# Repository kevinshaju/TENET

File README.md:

# __TENET__
WIRELESS DEVELOPMENT BOARD DESIGN

TENET is development board specifically designed for beginners and enthusiasts in the field of IoT and Robotics. At the heart of the board is the NINA-B302 microcontroller unit. The board also features the ESP-12F wireless chip for wireless connectivity. Incase if you're wondering how is it any different from other boards out there, then have a closer look at the design. TENET has an inbuilt DRV8833 motordriver which can be used to connect upto 2 motors without the need for any external shields. The board also has a Li-Po charging unit that can be used to power the board using a single cell Li-Po battery, which will come in handy while prototyping your next wireless robot.

The board also has quite a few sensors that you might need for your integrated Iot project. The details of all the features of the board are provided below:

1) 16 GPIO Headers
2) LSM9DS1-iNEMO Inertial Module
3) DRV8833 dual-H Bridge Motor Driver
4) LPS25HB Pressure Sensor
5) APDS-9960 Digital Proximity, Ambient Light, RGB and Gesture Sensor
6) HTS221 Capacitive digital sensor for relative humidity and temperature
7) ESP-12F WiFi Module

##  *"With TENET the only limit is your own imagination."*

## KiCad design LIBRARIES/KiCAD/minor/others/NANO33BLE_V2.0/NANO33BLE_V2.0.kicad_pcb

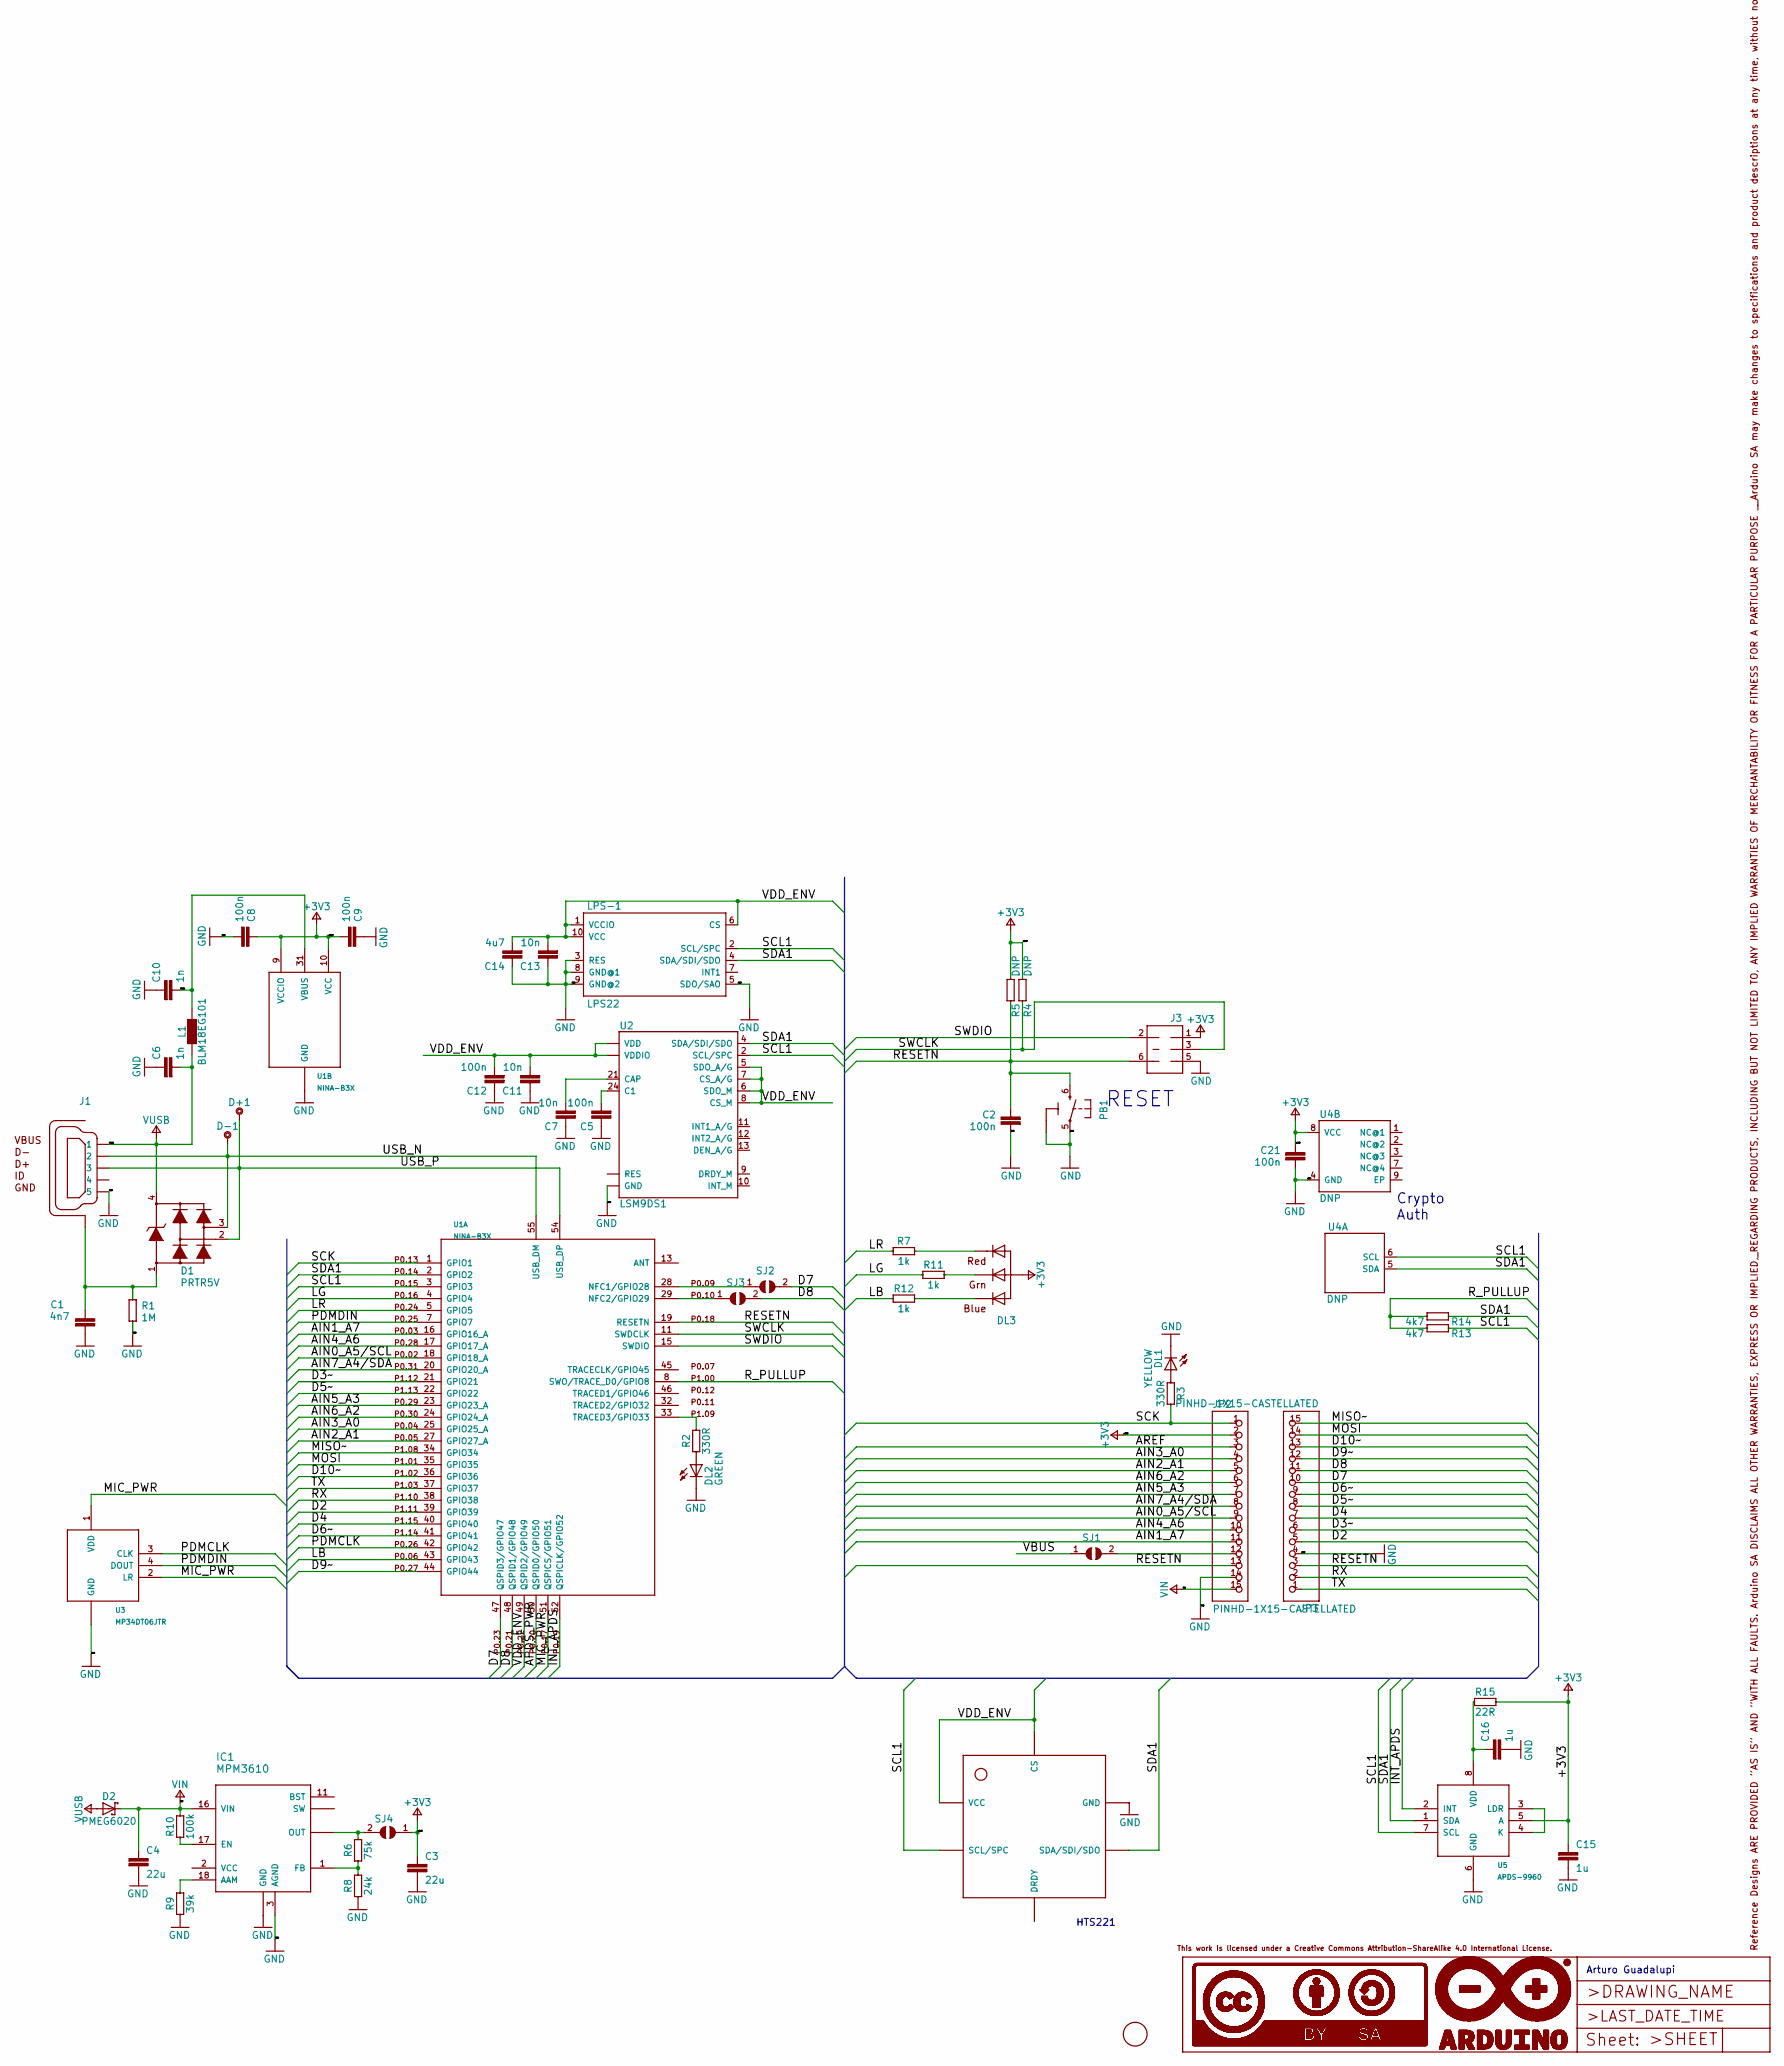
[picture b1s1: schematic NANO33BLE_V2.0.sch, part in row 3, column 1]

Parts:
C1: 4n7; 0805-R2013X50N; VOLTAGE 1KV
C2, C5, C8, C9, C12, C21: 100n; 0402-1005X55N
C3, C4: 22u; 0805-R2013X50N
C6, C10: 1n; 0402-1005X55N
C7, C11, C13: 10n; 0402-1005X55N
C14: 4u7; 0402-1005X55N
C15, C16: 1u; 0402-1005X55N
D1: PRTR5V; SOT190P230X110-4N
D2: PMEG6020; SODFL3517X110N
D+1: DNP; TP-1.00MM
D-1: DNP; TP-1.00MM
DL1: YELLOW; LEDC1608X80N-AK
DL2: GREEN; LEDC1608X80N-AK
DL3: -; SMLP34RGB2W
FD1: DNP; FD-1-1.5
FRAME1: DNP; FRAME
HS-1: HTS221
IC1: MPM3610
J1: -; ZX62-AB-5PA
J3: DNP; 2X03-TP1
JP2, JP3: PINHD-1X15-CASTELLATED; 1X15-CASTELL
L1: BLM18EG101; 0603-1608X90N
LPS-1: LPS22; LPS22H
PB1: PTS820; C&K_PTS820_NO_HOLES
R1: 1M; 0402-1005X55N
R2, R3: 330R; 0402-1005X55N
R4, R5: DNP; 0402-1005X55N
R6: 75k; 0402-1005X55N
R7, R11, R12: 1k; 0402-1005X55N
R8: 24k; 0402-1005X55N
R9: 39k; 0402-1005X55N
R10: 100k; 0402-1005X55N
R13, R14: 4k7; 0402-1005X55N
R15: 22R; 0402-1005X55N
SJ1, SJ2, SJ3, SJ4: DNP; SJ
U1: NINA-B3X
U2: LSM9DS1; LSM9DS1_TEMP_LGA24-8X4
U3: MP34DT06JTR; HCLGA
U4: DNP; SON50P300X200X60-9N-EP160X140
U5: APDS-9960; APDS9960

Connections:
+3V3: C3.1, C8.1, C9.2, C15.1, C21.1, DL3.1 (A), J3.1, JP2.2, R4.2, R5.2, R15.2, SJ4.1, U1.9 (VCCIO), U1.10 (VCC), U4.8 (VCC), U5.5 (A)
/AIN0_A5/SCL: JP2.9, U1.18 (GPIO18_A)
/AIN1_A7: JP2.11, U1.16 (GPIO16_A)
/AIN2_A1: JP2.5, U1.27 (GPIO27_A)
/AIN3_A0: JP2.4, U1.25 (GPIO25_A)
/AIN4_A6: JP2.10, U1.17 (GPIO17_A)
/AIN5_A3: JP2.7, U1.23 (GPIO23_A)
/AIN6_A2: JP2.6, U1.24 (GPIO24_A)
/AIN7_A4/SDA: JP2.8, U1.20 (GPIO20_A)
/APDS_PWR: U1.50 (QSPID0/GPIO50)
/AREF: JP2.3
/D2: JP3.5, U1.39 (GPIO39)
/D3~~: JP3.6, U1.21 (GPIO21)
/D4: JP3.7, U1.40 (GPIO40)
/D5~~: JP3.8, U1.22 (GPIO22)
/D6~~: JP3.9, U1.41 (GPIO41)
/D7: JP3.10, SJ2.2, U1.47 (QSPID3/GPIO47)
/D8: JP3.11, SJ3.2, U1.48 (QSPID1/GPIO48)
/D9~~: JP3.12, U1.44 (GPIO44)
/D10~~: JP3.13, U1.36 (GPIO36)
/INT_APDS: U1.52 (QSPICLK/GPIO52), U5.2 (INT)
/LB: R12.1, U1.43 (GPIO43)
/LG: R11.1, U1.4 (GPIO4)
/LR: R7.1, U1.5 (GPIO5)
/MIC_PWR: U1.51 (QSPICS/GPIO51), U3.1 (VDD), U3.2 (LR)
/MISO~~: JP3.15, U1.34 (GPIO34)
/MOSI: JP3.14, U1.35 (GPIO35)
/PDMCLK: U1.42 (GPIO42), U3.3 (CLK)
/PDMDIN: U1.7 (GPIO7), U3.4 (DOUT)
/RESETN: C2.1, J3.6, JP2.13, JP3.3, PB1.6 (2), R5.1, U1.19 (RESETN)
/RX: JP3.2, U1.38 (GPIO38)
/R_PULLUP: R13.2, R14.2, U1.8 (SWO/TRACE_D0/GPIO8)
/SCK: JP2.1, R3.2, U1.1 (GPIO1)
/SCL1: HS-1.P$2.SCL/SPC (SCL/SPC), LPS-1.2 (SCL/SPC), R13.1, U1.3 (GPIO3), U2.2 (SCL/SPC), U4.6 (SCL), U5.7 (SCL)
/SDA1: HS-1.P$4.SDA/SDI/SDO (SDA/SDI/SDO), LPS-1.4 (SDA/SDI/SDO), R14.1, U1.2 (GPIO2), U2.4 (SDA/SDI/SDO), U4.5 (SDA), U5.1 (SDA)
/SWCLK: J3.3, R4.1, U1.11 (SWDCLK)
/SWDIO: J3.2, U1.15 (SWDIO)
/TX: JP3.1, U1.37 (GPIO37)
/USB_N: D1.3, D-1.X, J1.2, U1.55 (USB_DM)
/USB_P: D1.2, D+1.X, J1.3, U1.54 (USB_DP)
/VBUS: C10.2, L1.2, SJ1.1, U1.31 (VBUS)
/VDD_ENV: C11.2, C12.2, C13.2, C14.2, HS-1.P$1.VDD (VCC), HS-1.P$6.CS (CS), LPS-1.1 (VCCIO), LPS-1.6 (CS), LPS-1.10 (VCC), U1.49 (QSPID2/GPIO49), U2.1 (VDDIO), U2.3 (VDDIO), U2.5 (SDO_A/G), U2.6 (SDO_M), U2.7 (CS_A/G), U2.8 (CS_M), U2.22 (VDD), U2.23 (VDD)
GND: C1.2, C2.2, C3.2, C4.2, C5.1, C6.1, C7.1, C8.2, C9.1, C10.1, C11.1, C12.1, C13.1, C14.1, C15.2, C16.2, C21.2, DL1.C, DL2.C, HS-1.P$5.GND (GND), IC1.3 (AGND), IC1.12 (GND), IC1.13 (GND), IC1.14 (GND), J1.5, J3.5, JP2.14, JP3.4, LPS-1.3 (RES), LPS-1.5 (SDO/SAO), LPS-1.8 (GND@1), LPS-1.9 (GND@2), PB1.1 (3), PB1.2 (3), PB1.3, PB1.4 (3), PB1.5 (1), R1.1, R8.1, R9.1, U1.6 (GND), U1.12 (GND), U1.14 (GND), U1.26 (GND), U1.30 (GND), U1.53 (GND), U1.GND@1 (GND), U1.GND@2 (GND), U1.GND@3 (GND), U1.GND@4 (GND), U1.GND@5 (GND), U1.GND@6 (GND), U1.GND@7 (GND), U1.GND@8 (GND), U1.GND@9 (GND), U1.GND@10 (GND), U1.GND@11 (GND), U1.GND@12 (GND), U2.19 (GND), U2.20 (GND), U3.GND, U3.GND@2 (GND), U3.GND@3 (GND), U3.GND@4 (GND), U4.4 (GND), U5.6 (GND)
unnamed: C1.1, D1.1, J1.6 (SH), J1.7 (SH), J1.8 (SH), J1.9 (SH), J1.10 (SH), J1.11 (SH), R1.2
unnamed: C5.2, U2.24 (C1)
unnamed: C7.2, U2.21 (CAP)
unnamed: C16.1, R15.1, U5.8 (VDD)
unnamed: DL1.A, R3.1
unnamed: DL2.A, R2.1
unnamed: DL3.2 (RED_C), R7.2
unnamed: DL3.3 (BLUE_C), R12.2
unnamed: DL3.4 (GREEN_C), R11.2
unnamed: IC1.1 (FB), R6.1, R8.2
unnamed: IC1.17 (EN), R10.1
unnamed: IC1.18 (AAM), R9.2
unnamed: IC1.4 (SW), IC1.5 (SW), IC1.6 (SW), IC1.19 (SW)
unnamed: IC1.7 (OUT), IC1.8 (OUT), IC1.9 (OUT), IC1.20 (OUT), R6.2, SJ4.2
unnamed: JP2.12, SJ1.2
unnamed: R2.2, U1.33 (TRACED3/GPIO33)
unnamed: SJ2.1, U1.28 (NFC1/GPIO28)
unnamed: SJ3.1, U1.29 (NFC2/GPIO29)
unnamed: U2.14 (RES), U2.15 (RES), U2.16 (RES), U2.17 (RES), U2.18 (RES)
unnamed: U5.3 (LDR), U5.4 (K)
VIN: C4.1, D2.C, IC1.16 (VIN), JP2.15, R10.2
VUSB: C6.2, D1.4, D2.A, J1.1, L1.1

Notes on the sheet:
RESET
Crypto Auth
Arturo Guadalupi
HTS221

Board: 2 copper layers, 58 parts (0 on the bottom side), 63 nets, no tracks yet.

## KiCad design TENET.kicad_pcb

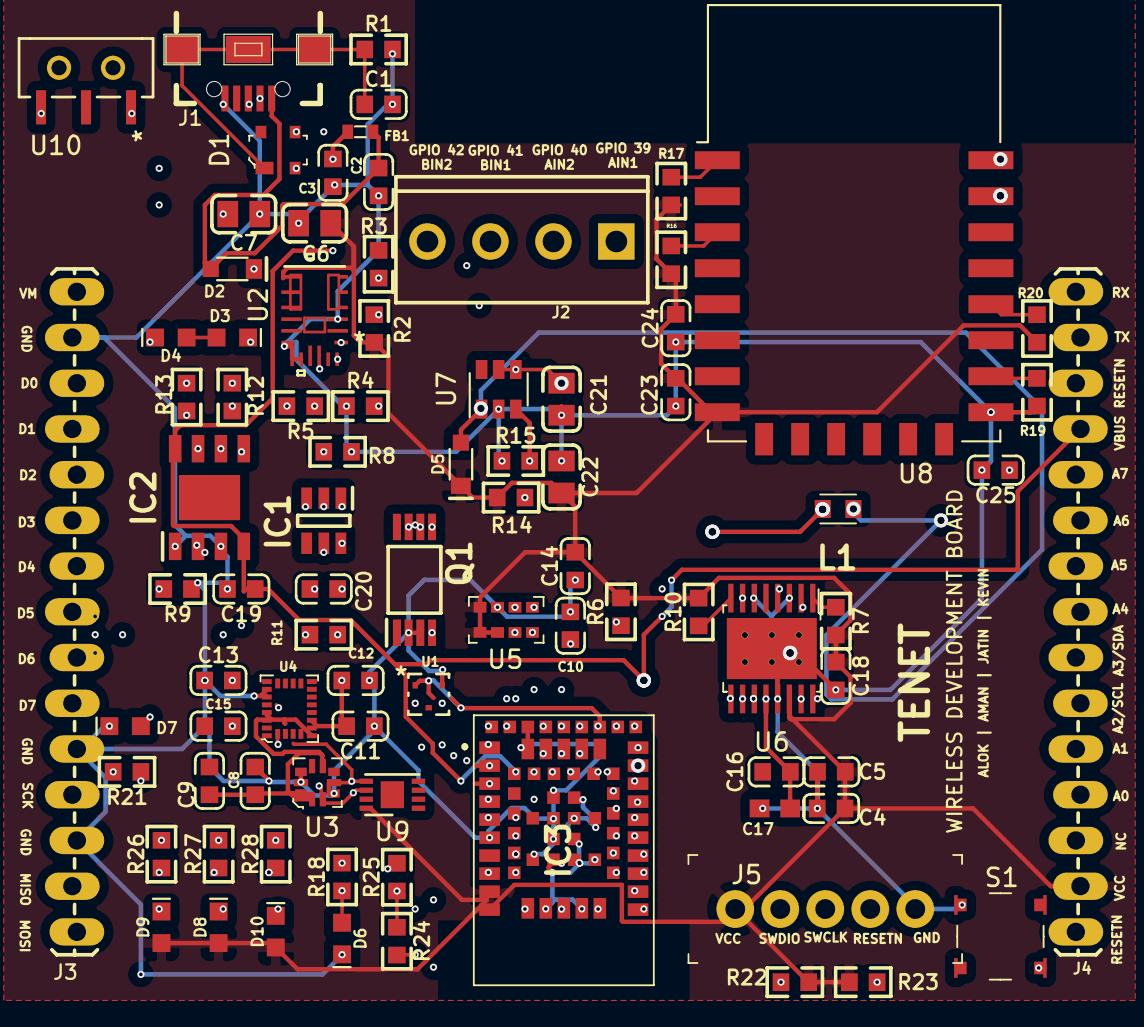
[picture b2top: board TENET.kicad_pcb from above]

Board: 4 copper layers, 86 parts (1 on the bottom side), 83 nets.

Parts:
C1, C2, C3, C4, C5, C8, C9, C10, C11, C12, C13, C14, C15, C16, C18, C19, C20, C23, C24, C25: C_0603
C6, C7, C21, C22: C_0805
C17: 0603-POLAR
D1: TO-253-4
D2, D5: PANASONIC_SMINI2-F5-B
D3, D4, D6, D7, D8, D9, D10: LED-0603
FB1: BLM18PG121SN1D; 0603
IC1: SOT95P280X145-6N
IC2: SOIC127P600X175-9N
IC3: NINAB30200B00
J1: USB-B-MICRO-SMD
J2: SCREWTERMINAL-3.5MM-4
J3, J4: 1X15_LOCK_LONGPADS
J5: PinHeader_1x5_P2.5mm_Drill1.1mm
J6: JST-2-SMD
L1: LQH2MCN100K02L
Q1: SOP65P640X120-8N
R1, R2, R3, R4, R5, R6, R7, R8, R9, R10, R11, R12, R13, R14, R15, R16, R17, R18, R19, R20, R21, R22, R23, R24, R25, R26, R27, R28: R_0603
S1: Switch_Tactile_SMD_4.5x4.5mm_TL3315NF160Q
U1: HTS221TR
U2: MPM3610AGQV-Z
U3: LLGA-10_2.5x2.5mm_LPS25HB
U4: LGA-24_3x3.5mm_LSM9DS1
U5: Ambient_Prox_APDS-9960
U6: TSSOP-16-1EP_W4.40mm
U7: SOT-23-6
U8: ESP-12E
U9: DFN-8-1EP_3x2mm_P0.5mm_EP1.3x1.5mm
U10: AYZ0102AGRLC

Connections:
A0: IC3.16, J4.4
A1: IC3.17, J4.5
A2\SCL: IC3.18, J4.6
A3\SDA: IC3.20, J4.7
A4: IC3.23, J4.8
A5: IC3.24, J4.9
A6: IC3.25, J4.10
A7: IC3.27, J4.11
AIN1: IC3.39, U6.16
AIN2: IC3.40, U6.15
BAT+: IC2.5, J6.2, R11.1, U10.3
BAT-: C20.2, IC1.6, J6.1, Q1.6, Q1.7
BIN1: IC3.41, U6.9
BIN2: IC3.42, U6.10
D0: IC3.21, J3.3
D1: IC3.22, J3.4
D2: IC3.28, J3.5
D3: IC3.29, J3.6
D4: IC3.36, J3.7
D5: IC3.44, J3.8
D6: IC3.47, J3.9
D7: IC3.48, J3.10
D+: D1.2, IC3.54, J1.D+
D-: D1.3, IC3.55, J1.D-
GND: C1.2, C2.1, C3.1, C4.1, C5.2, C6.1, C7.1, C8.1, C9.1, C10.2, C11.1, C12.1, C13.1, C14.1, C15.1, C17.-, C18.2, C19.2, C21.1, C22.1, C23.2, C24.1, C25.2, D6.C, D7.C, IC2.1, IC2.3, IC3.6, IC3.12, IC3.14, IC3.26, IC3.30, IC3.53, IC3.G1, IC3.G2, IC3.G3, IC3.G4, IC3.G5, IC3.G6, IC3.G7, IC3.G8, IC3.G9, IC3.G10, IC3.G11, IC3.G12, J1.GND, J3.2, J3.11, J3.13, J5.5, Q1.2, Q1.3, R1.2, R3.1, R4.1, R8.1, R9.1, R15.1, R19.2, S1.4, U1.5, U2.3, U2.12, U2.13, U2.14, U3.3, U3.5, U3.8, U3.9, U4.19, U4.20, U5.6, U6.3, U6.6, U6.13, U6.17, U7.2, U8.15, U9.4
INT_APDS: IC3.52, U5.2
LB: IC3.43, R28.2
LG: IC3.4, R26.2
LR: IC3.5, R27.2
MISO: IC3.34, J3.14
MOSI: IC3.35, J3.15
unnamed: C1.1, D1.1, J1.SHIE, R1.1
unnamed: C7.2, D2.C, R5.2, U2.16
unnamed: C10.1, R6.1, U5.8
unnamed: C13.2, U4.21
unnamed: C15.2, U4.24
unnamed: C16.2, U6.11
unnamed: C20.1, IC1.5, R11.2
unnamed: C21.2, L1.1, U7.4, U7.5, U10.1
unnamed: D3.A, D4.A
unnamed: D3.C, R12.2
unnamed: D4.C, R13.1
unnamed: D5.A, L1.2, U7.1
unnamed: D6.A, R18.1
unnamed: D7.A, R21.1
unnamed: D8.C, R27.1
unnamed: D9.C, R26.1
unnamed: D10.C, R28.1
unnamed: IC1.1, Q1.5
unnamed: IC1.2, R8.2
unnamed: IC1.3, Q1.4
unnamed: IC2.2, R9.2
unnamed: IC2.6, R12.1
unnamed: IC2.7, R13.2
unnamed: IC3.33, R18.2
unnamed: J2.1, U6.2
unnamed: J2.2, U6.4
unnamed: J2.3, U6.7
unnamed: J2.4, U6.5
unnamed: R2.2, R3.2, U2.1
unnamed: R4.2, U2.18
unnamed: R5.1, U2.17
unnamed: R7.1, U6.1
unnamed: R10.1, U6.8
unnamed: R14.2, R15.2, U7.3
unnamed: R16.2, U8.3
unnamed: R17.2, U8.1
unnamed: R19.1, U8.16
unnamed: R20.1, U8.18
RESETN: C25.1, IC3.19, J4.1, J4.13, J5.4, R23.1, S1.1
RX: IC3.38, J4.15, U8.21
R_PULLUP: IC3.8, R24.1, R25.1
SCK: IC3.1, J3.12, R21.2
SCL: IC3.3, R24.2, U1.2, U3.2, U4.2, U5.7, U9.6
SDA: IC3.2, R25.2, U1.4, U3.4, U4.4, U5.1, U9.5
SWCLK: IC3.11, J5.3, R22.2
SWDIO: IC3.15, J5.2
TX: IC3.37, J4.14, U8.22
VBUS: C3.2, C19.1, FB1.2, IC2.4, IC2.8, IC3.31, J4.12
VCC: C4.2, C5.1, C6.2, C14.2, C18.1, C22.2, C23.1, C24.2, D5.C, D8.A, D9.A, D10.A, IC3.9, IC3.10, J4.2, J5.1, R2.1, R6.2, R7.2, R10.2, R14.1, R16.1, R17.1, R20.2, R22.1, R23.2, U2.7, U2.8, U2.9, U5.3, U5.4, U5.5, U6.14, U8.8, U9.8
VDD_ENV: C8.2, C9.2, C11.2, C12.2, IC3.49, U1.1, U1.6, U3.1, U3.6, U3.10, U4.1, U4.3, U4.5, U4.6, U4.7, U4.8, U4.22, U4.23
VM: C16.1, C17.+, J3.1, U6.12
VUSB: C2.2, D2.A, FB1.1, J1.VBUS

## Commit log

2020-09-24 All Files

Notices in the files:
parts and their libraries:
Copyright 2016 Accelerated Designs. All rights reserved.
